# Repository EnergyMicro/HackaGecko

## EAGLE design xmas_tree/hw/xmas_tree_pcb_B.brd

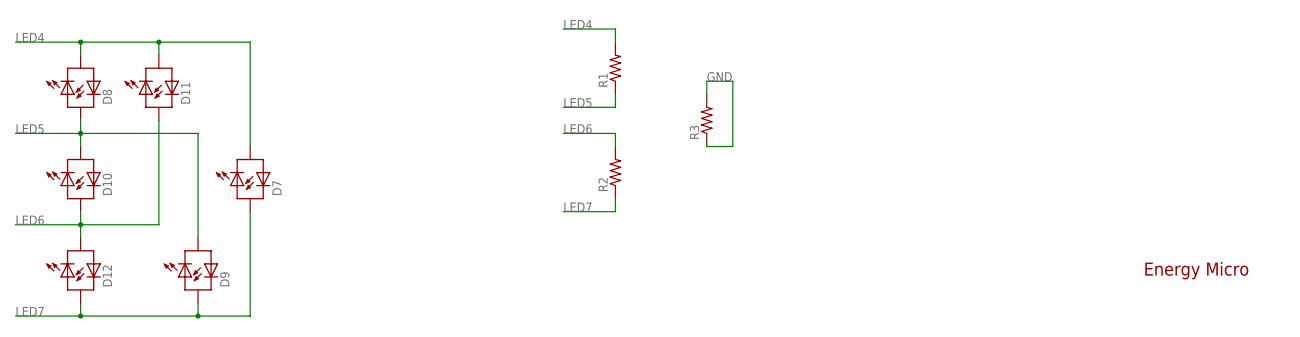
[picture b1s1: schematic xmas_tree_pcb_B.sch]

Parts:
D7, D8, D9, D10, D11, D12: LED_BI_COLOR; LED3MM
R1, R2, R3: RESISTOR1206; 1206

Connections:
GND: R3.1, R3.2
LED4: D7.K (C1), D8.K (C1), D11.K (C1), R1.2
LED5: D8.A (A1), D9.K (C1), D10.K (C1), R1.1
LED6: D10.A (A1), D11.A (A1), D12.K (C1), R2.2
LED7: D7.A (A1), D9.A (A1), D12.A (A1), R2.1

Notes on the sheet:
Energy Micro

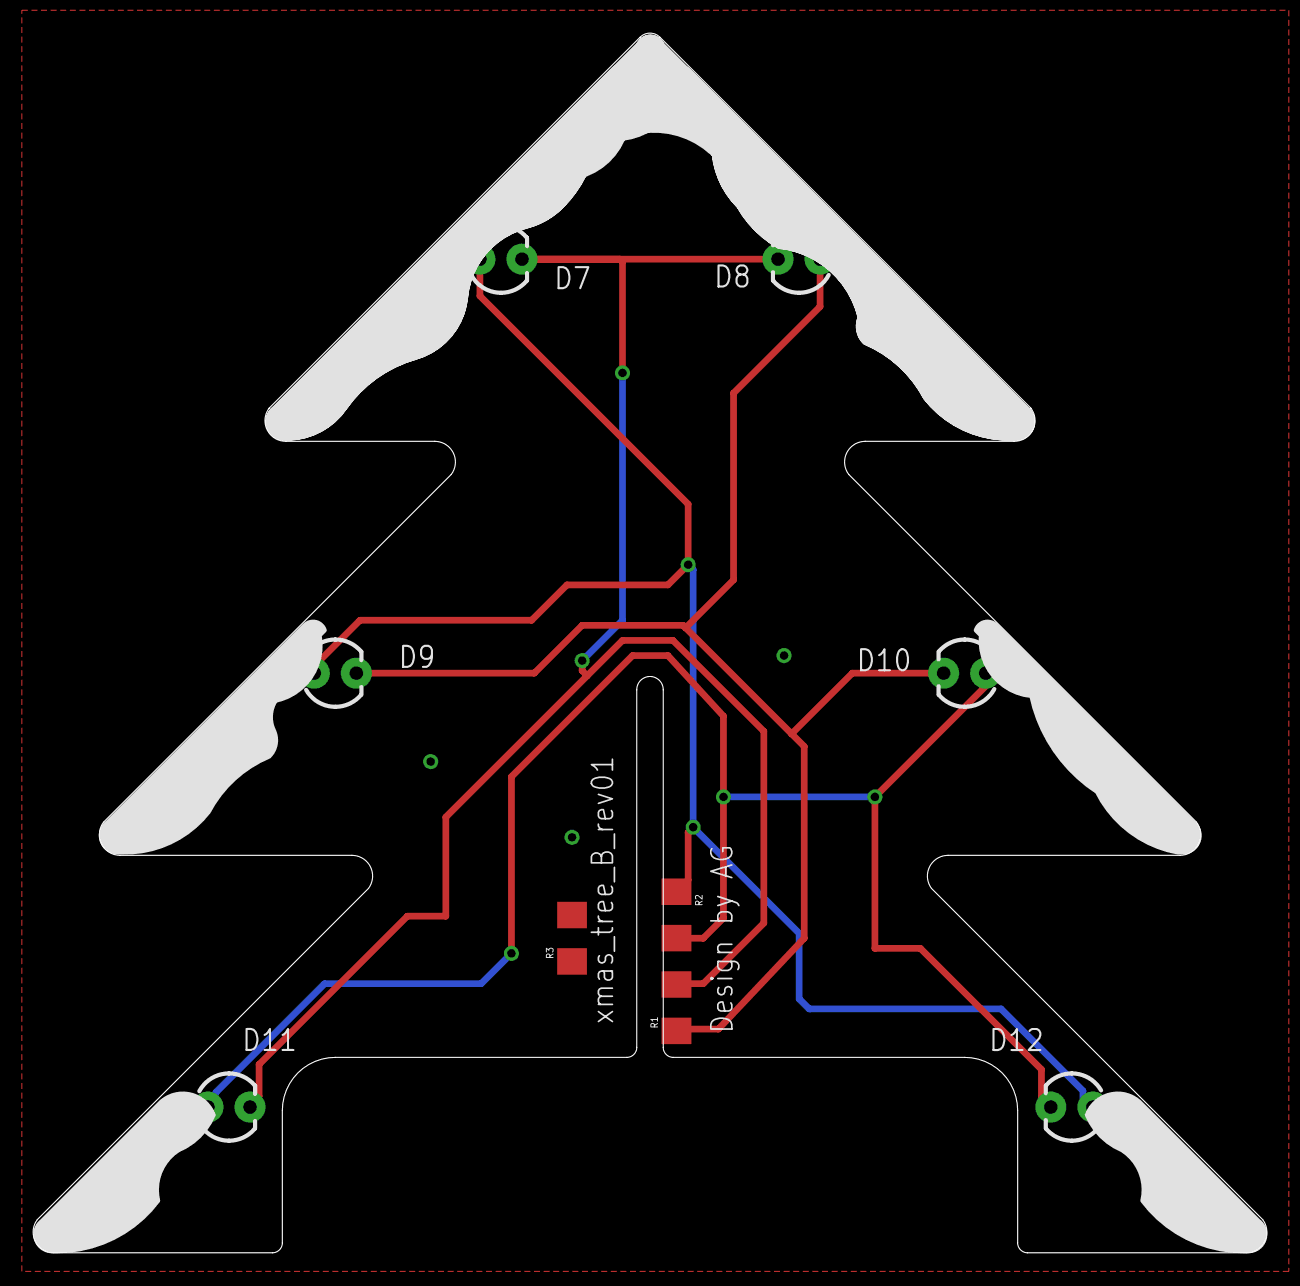
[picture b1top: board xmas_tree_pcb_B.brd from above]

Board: 2 copper layers, 74.5 x 73.6 mm, 9 parts (0 on the bottom side), 5 nets.

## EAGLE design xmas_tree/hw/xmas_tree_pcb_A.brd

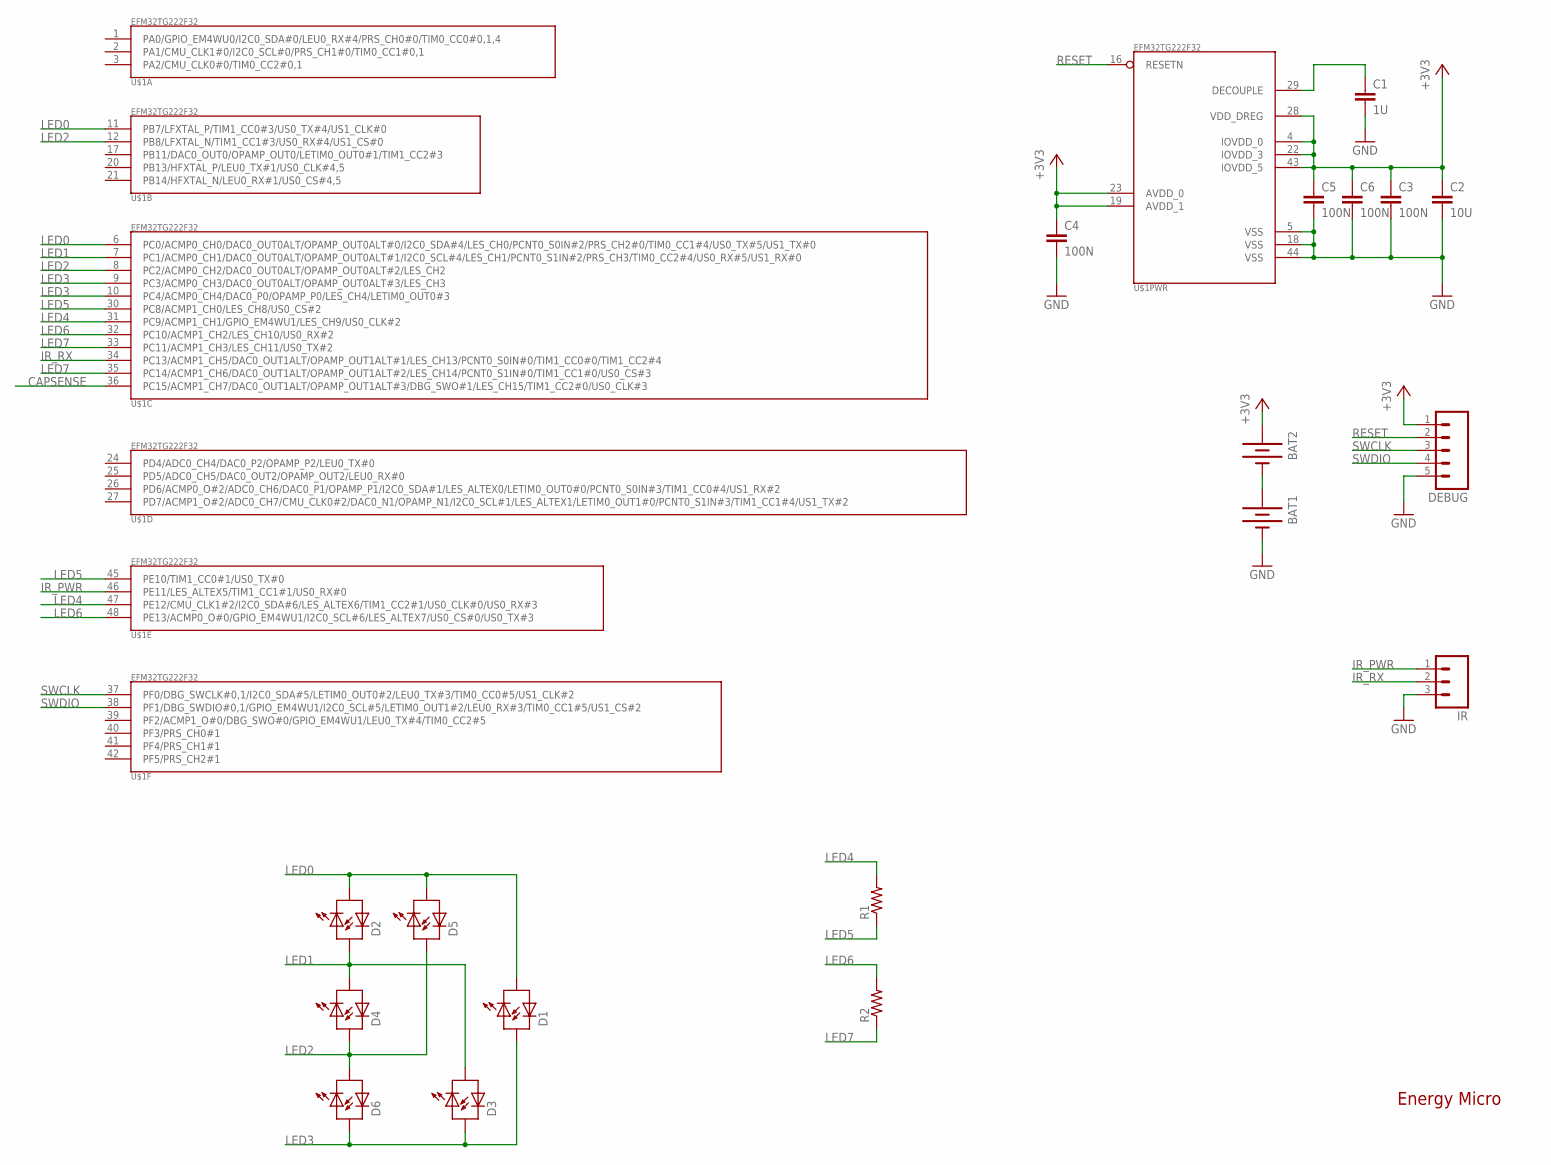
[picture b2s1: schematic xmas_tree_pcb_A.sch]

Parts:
BAT1, BAT2: BATTERYAAA; BATTERY-AAA
C1: 1U; C0603
C2: 10U; C0603
C3, C4, C5, C6: 100N; C0603
D1, D2, D3, D4, D5, D6: LED_BI_COLOR; LED3MM
DEBUG: M05LOCK; 1X05_LOCK
IR: M03LOCK; 1X03_LOCK
R1, R2: RESISTOR1206; 1206
U$1: EFM32TG222F32; QFP48

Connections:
+3V3: BAT2.PWR@1 (+), C2.1, C3.1, C4.1, C5.1, C6.1, DEBUG.1, U$1.4 (IOVDD_0), U$1.19 (AVDD_1), U$1.22 (IOVDD_3), U$1.23 (AVDD_0), U$1.28 (VDD_DREG), U$1.43 (IOVDD_5)
CAPSENSE: U$1.36 (PC15/ACMP1_CH7/DAC0_OUT1ALT/OPAMP_OUT1A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)
GND: BAT1.GND@1 (-), C1.2, C2.2, C3.2, C4.2, C5.2, C6.2, DEBUG.5, IR.3, U$1.5 (VSS), U$1.18 (VSS), U$1.44 (VSS)
IR_PWR: IR.1, U$1.46 (PE11/LES_ALTEX5/TIM1_CC1#1/US0_RX#0)
IR_RX: IR.2, U$1.34 (PC13/ACMP1_CH5/DAC0_OUT1ALT/OPAMP_OUT1A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)
LED0: D1.K (C1), D2.K (C1), D5.K (C1), U$1.6 (PC0/ACMP0_CH0/DAC0_OUT0ALT/OPAMP_OUT0AL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), U$1.11 (PB7/LFXTAL_P/TIM1_CC0#3/US0_TX#4/US1_CL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)
LED1: D2.A (A1), D3.K (C1), D4.K (C1), U$1.7 (PC1/ACMP0_CH1/DAC0_OUT0ALT/OPAMP_OUT0AL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)
LED2: D4.A (A1), D5.A (A1), D6.K (C1), U$1.8 (PC2/ACMP0_CH2/DAC0_OUT0ALT/OPAMP_OUT0AL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), U$1.12 (PB8/LFXTAL_N/TIM1_CC1#3/US0_RX#4/US1_CS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)
LED3: D1.A (A1), D3.A (A1), D6.A (A1), U$1.9 (PC3/ACMP0_CH3/DAC0_OUT0ALT/OPAMP_OUT0AL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), U$1.10 (PC4/ACMP0_CH4/DAC0_P0/OPAMP_P0/LES_CH4/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)
LED4: R1.2, U$1.31 (PC9/ACMP1_CH1/GPIO_EM4WU1/LES_CH9/US0_C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), U$1.47 (PE12/CMU_CLK1#2/I2C0_SDA#6/LES_ALTEX6/T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)
LED5: R1.1, U$1.30 (PC8/ACMP1_CH0/LES_CH8/US0_CS#2), U$1.45 (PE10/TIM1_CC0#1/US0_TX#0)
LED6: R2.2, U$1.32 (PC10/ACMP1_CH2/LES_CH10/US0_RX#2), U$1.48 (PE13/ACMP0_O#0/GPIO_EM4WU1/I2C0_SCL#6/L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)
LED7: R2.1, U$1.33 (PC11/ACMP1_CH3/LES_CH11/US0_TX#2), U$1.35 (PC14/ACMP1_CH6/DAC0_OUT1ALT/OPAMP_OUT1A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)
unnamed: C1.1, U$1.29 (DECOUPLE)
unnamed: BAT1.PWR@1 (+), BAT2.GND@1 (-)
RESET: DEBUG.2, U$1.16 (RESETN)
SWCLK: DEBUG.3, U$1.37 (PF0/DBG_SWCLK#0,1/I2C0_SDA#5/LETIM0_OUT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)
SWDIO: DEBUG.4, U$1.38 (PF1/DBG_SWDIO#0,1/GPIO_EM4WU1/I2C0_SCL#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)

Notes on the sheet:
Energy Micro

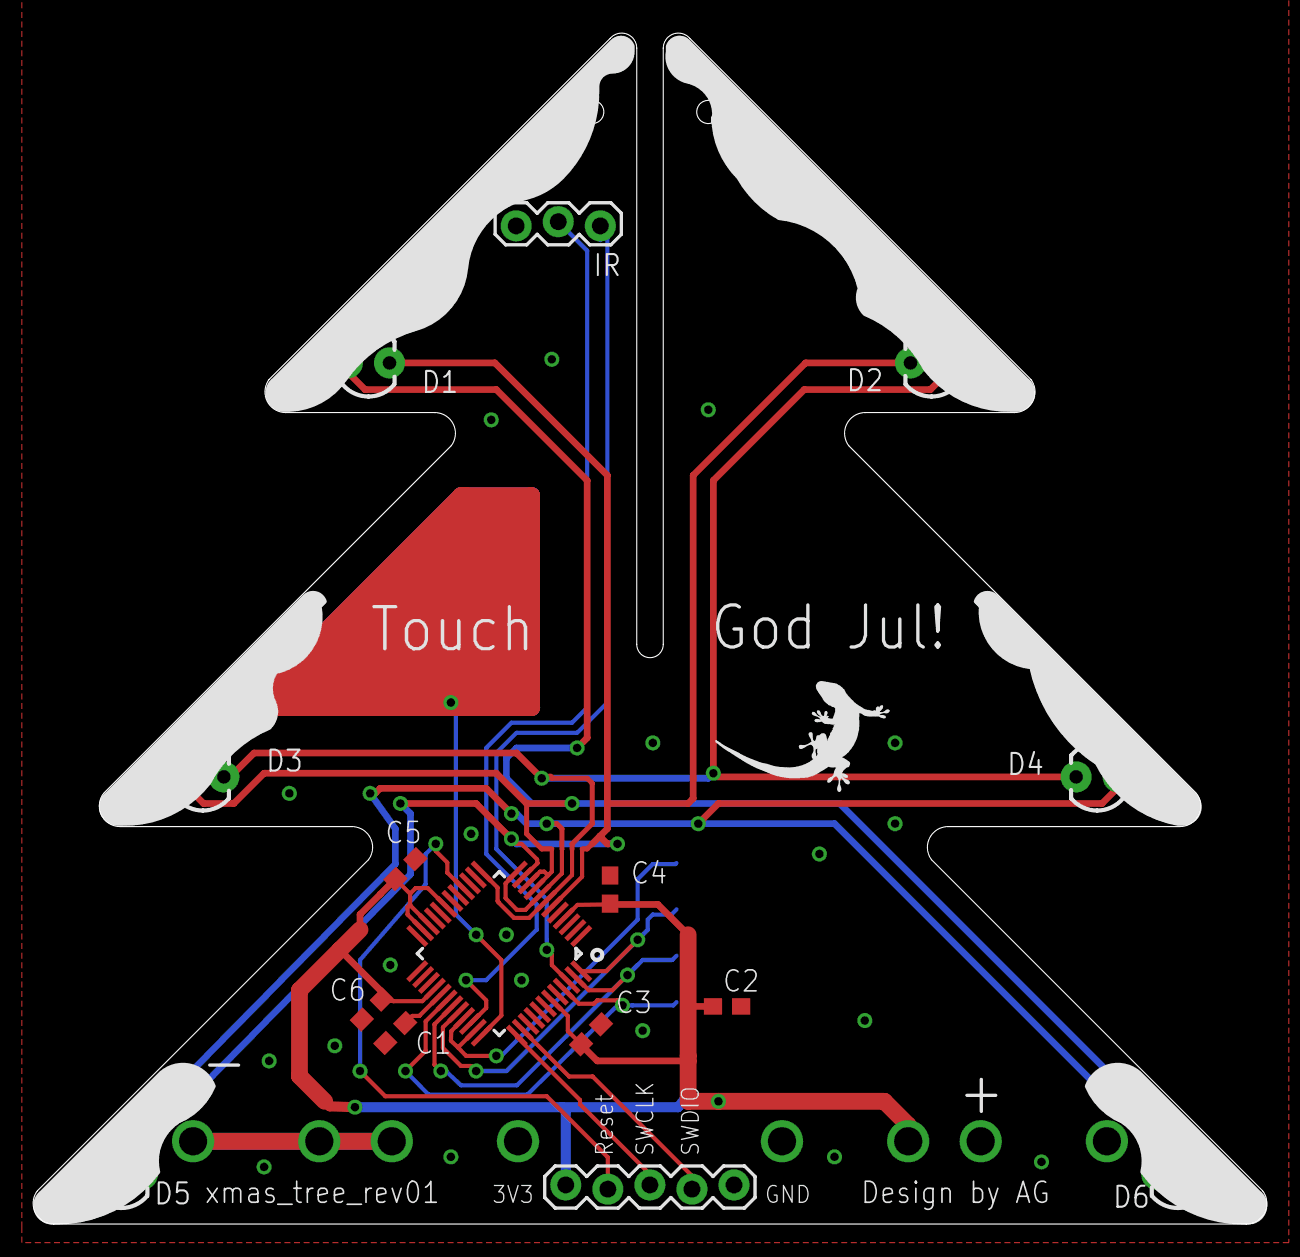
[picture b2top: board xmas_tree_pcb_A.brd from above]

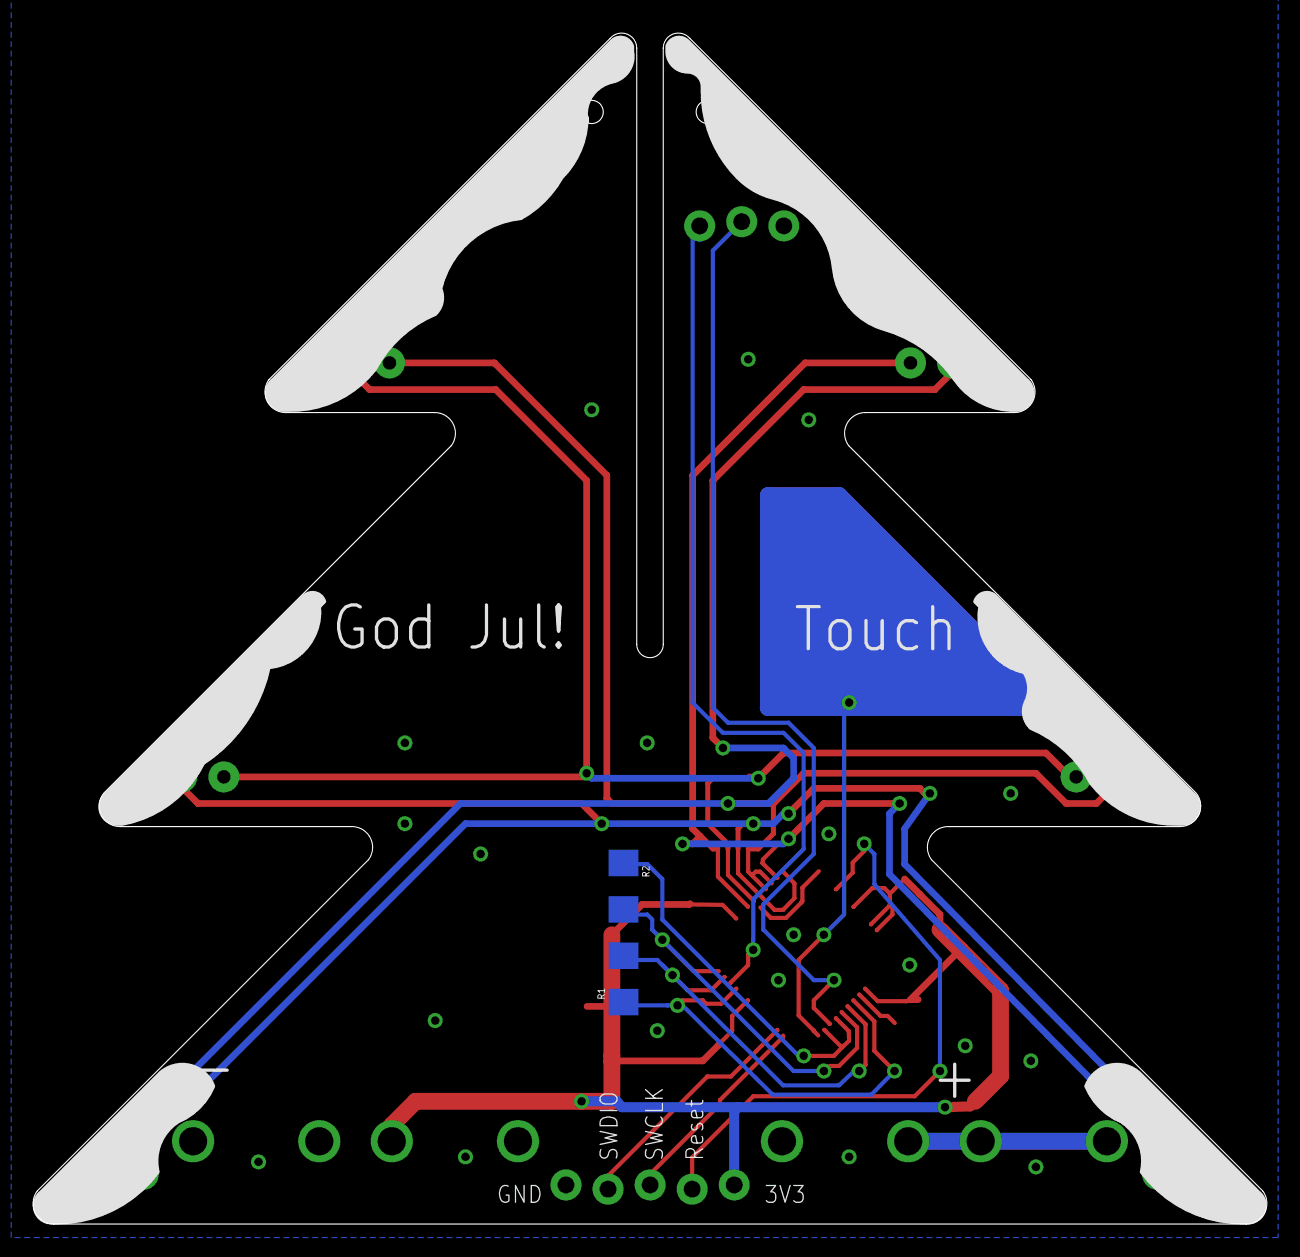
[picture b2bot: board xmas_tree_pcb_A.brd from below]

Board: 2 copper layers, 74.5 x 71.9 mm, 21 parts (3 on the bottom side), 17 nets.

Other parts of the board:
U$2: GECKO_BOTTOM
U$30: GECKO

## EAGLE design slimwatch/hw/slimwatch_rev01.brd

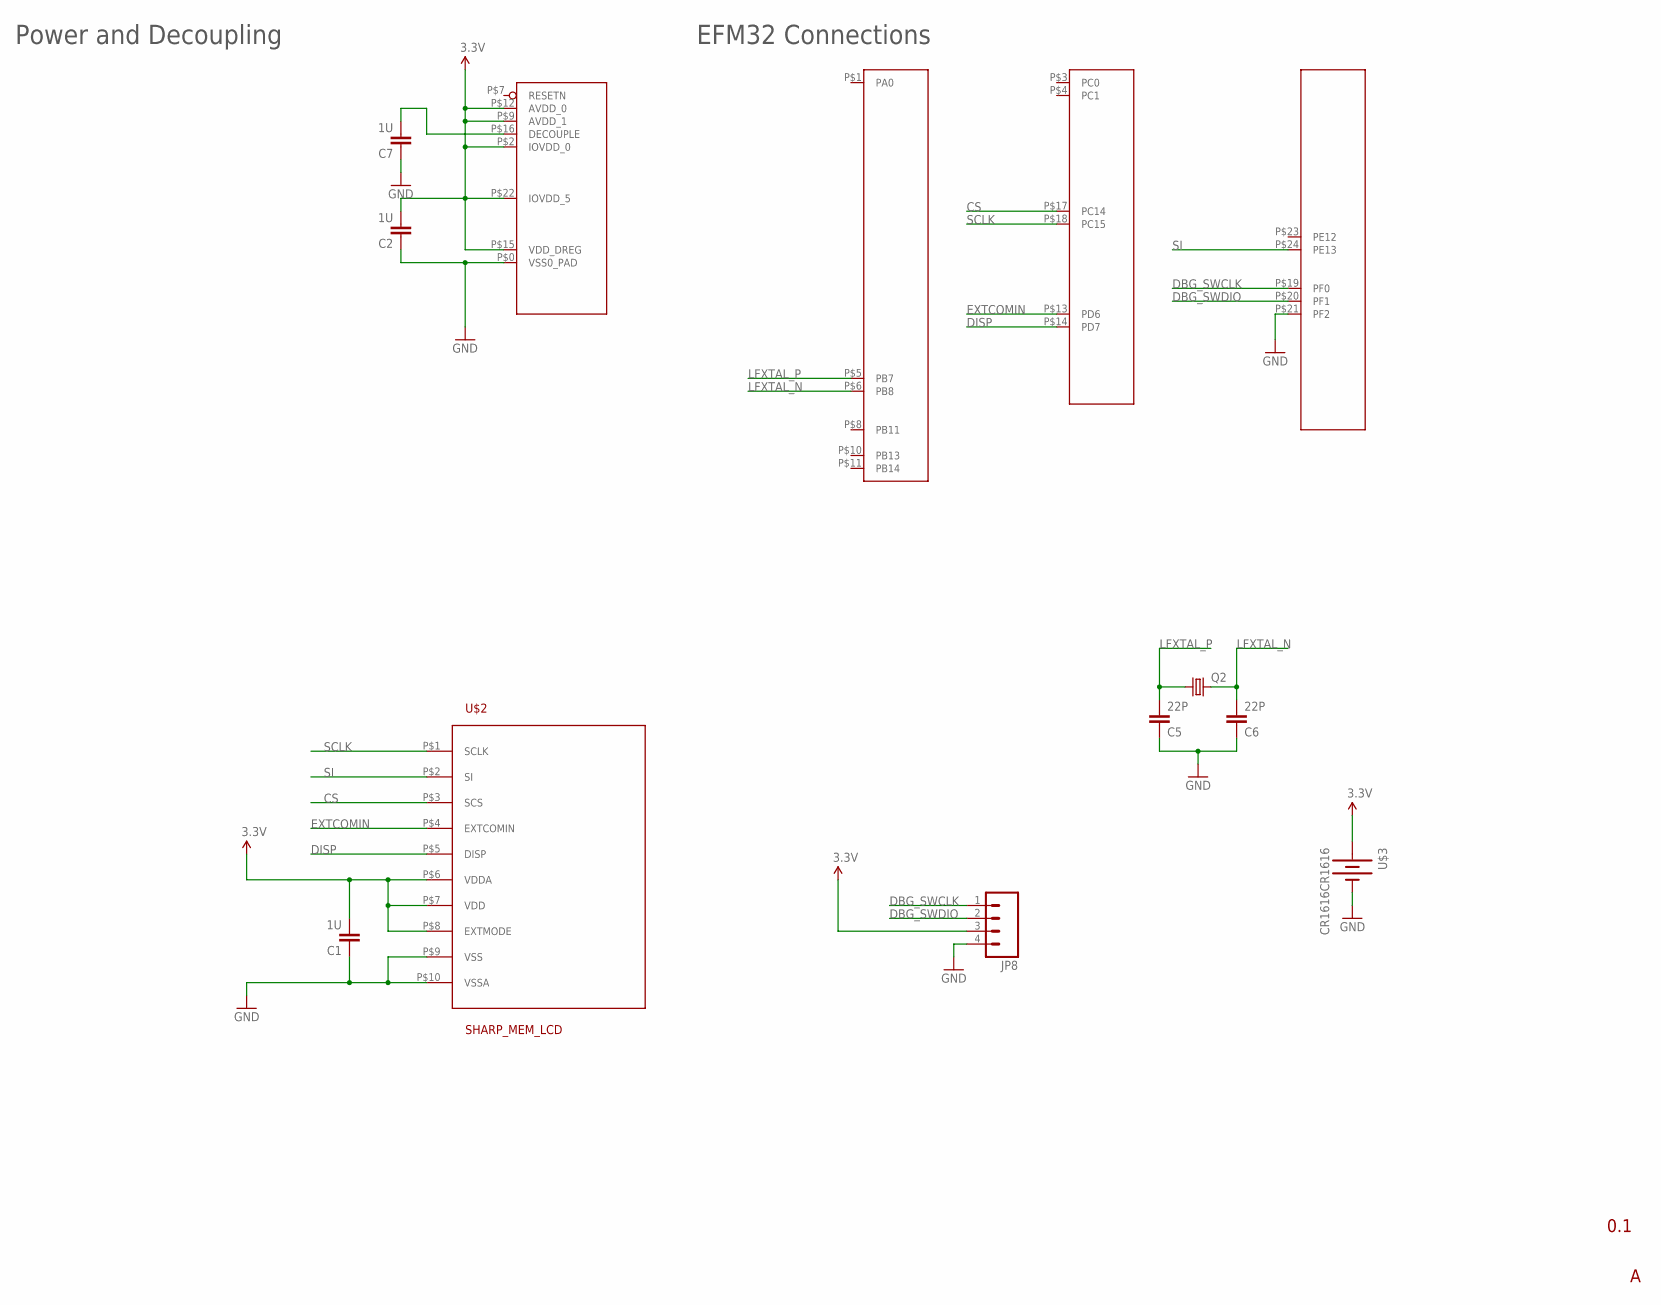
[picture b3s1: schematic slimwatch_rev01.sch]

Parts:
C1, C2, C7: 1U; C0603
C5, C6: 22P; C0603
JP8: M04LOCK; 1X04_LOCK
Q2: CRYSTAL; ABRACON_32KHZ_CRYSTAL
U$1: EFM32GG980; QFN24
U$2: SHARP_MEM_LCD
U$3: CR1616CR1616; BATTCON_16MM

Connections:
3.3V: C1.2, C2.2, JP8.3, U$1.P$2 (IOVDD_0), U$1.P$9 (AVDD_1), U$1.P$12 (AVDD_0), U$1.P$15 (VDD_DREG), U$1.P$22 (IOVDD_5), U$2.P$6 (VDDA), U$2.P$7 (VDD), U$2.P$8 (EXTMODE), U$3.P$2 (+), U$3.P$3 (+)
CS: U$1.P$17 (PC14), U$2.P$3 (SCS)
DBG_SWCLK: JP8.1, U$1.P$19 (PF0)
DBG_SWDIO: JP8.2, U$1.P$20 (PF1)
DISP: U$1.P$14 (PD7), U$2.P$5 (DISP)
EXTCOMIN: U$1.P$13 (PD6), U$2.P$4 (EXTCOMIN)
GND: C1.1, C2.1, C5.1, C6.1, C7.1, JP8.4, U$1.P$0 (VSS0_PAD), U$1.P$21 (PF2), U$2.P$9 (VSS), U$2.P$10 (VSSA), U$3.P$1 (-)
LFXTAL_N: C6.2, Q2.P$2 (2), U$1.P$6 (PB8)
LFXTAL_P: C5.2, Q2.P$1 (1), U$1.P$5 (PB7)
unnamed: C7.2, U$1.P$16 (DECOUPLE)
SCLK: U$1.P$18 (PC15), U$2.P$1 (SCLK)
SI: U$1.P$24 (PE13), U$2.P$2 (SI)

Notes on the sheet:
EFM32 Connections
Power and Decoupling
0.1

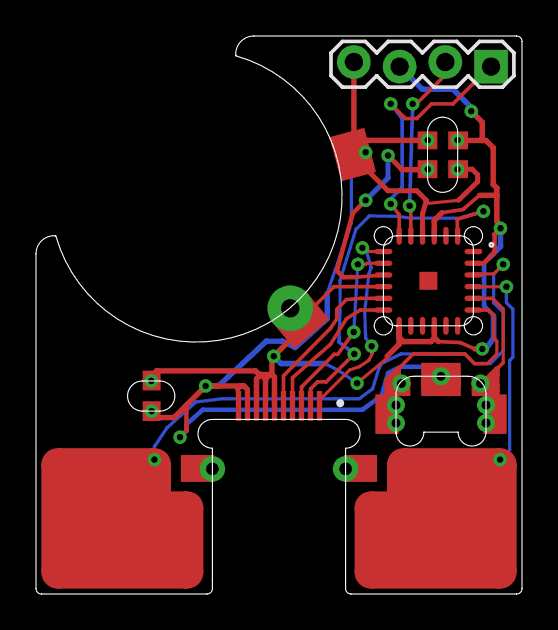
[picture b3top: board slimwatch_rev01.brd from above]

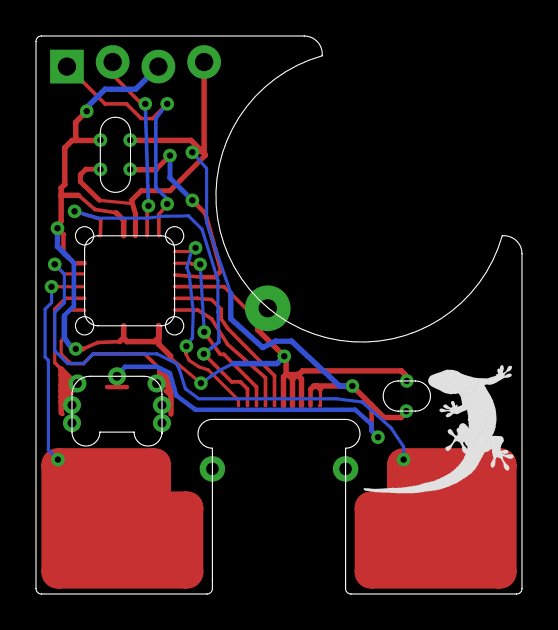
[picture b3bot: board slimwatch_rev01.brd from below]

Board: 2 copper layers, 27.0 x 31.0 mm, 12 parts (2 on the bottom side), 12 nets.

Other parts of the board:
U$4: GECKO
U$5: GECKO_BOTTOM

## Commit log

2012-09-06 test
2012-11-09 added ikea dioder driver files
2012-11-09 test.txt removed
2012-11-09 renamed files
2012-11-09 added pulse oximeter efm32 code
2012-11-09 added pulse oximeter pc code
2012-12-20 Added necessary parts from Nokia Embedded Widgets demo missing in the original upload.
2013-01-03 added slimwatch
2013-01-03 added xmas tree
2013-01-09 Added arcade joystick code
2013-04-18 twelve bottles one giant project added
2013-05-10 added nprint example
2013-05-10 removed xml file
2013-05-10 Restored nprint/genproject/nanoprint.xml
2013-05-30 Added Kicad_3D project
2013-07-16 added gps_logger
2013-07-16 added microsdconfig.h to gps_logger
2013-07-17 updated readme.txt for gps_logger
2013-09-05 added arkanoid project

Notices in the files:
parts and their libraries:
EnergyMicro: CC0 License
